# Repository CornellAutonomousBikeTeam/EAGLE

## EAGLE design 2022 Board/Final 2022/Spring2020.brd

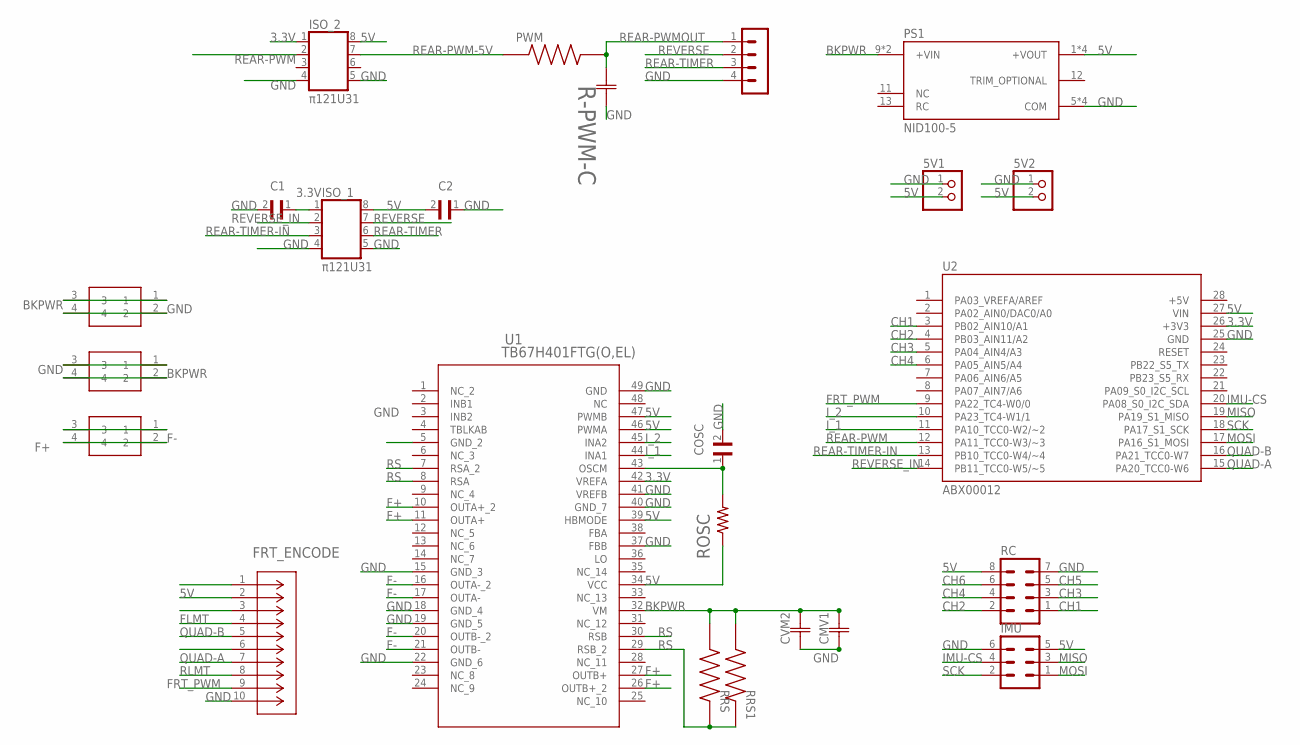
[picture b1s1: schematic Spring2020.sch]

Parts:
5V1, 5V2: PINHD-1X2; 1X02
C1, C2: CL05A105KP5NNNC; CAPC1005X55N
CMV1: UVY1H102MHD; CAP_12.5_X_25_NCH
COSC: GRM022R71A271KA01L; CAPC0402X22N
CVM2: CL05B104KB54PNC; CAP_CL_05_SAM
FRT_ENCODE: 3220-10-0100-00; CONN_3220-10-0100-00_CNC
FRT_MTR: 2060-452_998-404; 2060452998404
IMU: MA03-2
ISO_1, ISO_2: π121U31; SO08
PS1: NID100-5; CONV_NID100-5
PWM: ERJ1GNF6802C; RES_ERJ1GNF6802C
PWR_IN: 2060-452_998-404; 2060452998404
R-PWM-C: CL03A105MQ3CSNC; CAP_CL03_SAM
RC: MA04-2
REAR-MOTOR: MA04-1
REAR_PWR: 2060-452_998-404; 2060452998404
ROSC: R-US_R0402; R0402
RRS, RRS1: RLP73K3AR22FTDF; RESC6331X70N
U1: TB67H401FTG(O,EL); P-VQFN48-0707-0P50-004_TOS
U2: ABX00012; ARDUINO_ABX00012

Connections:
3.3V: C1.1, ISO_1.1, ISO_2.1, U1.42 (VREFA), U2.26 (+3V3)
5V: 5V1.2, 5V2.2, C2.2, FRT_ENCODE.2, IMU.5, ISO_1.8, ISO_2.8, PS1.1 (+VOUT), PS1.2 (+VOUT), PS1.3 (+VOUT), PS1.4 (+VOUT), RC.8, ROSC.1, U1.34 (VCC), U1.39 (HBMODE), U1.46 (PWMA), U1.47 (PWMB), U2.27 (VIN)
+5V: U2.28 (+5V)
BKPWR: CMV1.2, CVM2.2, PS1.9 (+VIN), PS1.10 (+VIN), PWR_IN.1, PWR_IN.3, REAR_PWR.2, REAR_PWR.4, RRS.1, RRS1.1, U1.32 (VM)
CH1: RC.1, U2.3 (PB02_AIN10/A1)
CH2: RC.2, U2.4 (PB03_AIN11/A2)
CH3: RC.3, U2.5 (PA04_AIN4/A3)
CH4: RC.4, U2.6 (PA05_AIN5/A4)
CH5: RC.5
CH6: RC.6
F+: FRT_MTR.2, FRT_MTR.4, U1.10 (OUTA+_2), U1.11 (OUTA+), U1.26 (OUTB+_2), U1.27 (OUTB+)
F-: FRT_MTR.1, FRT_MTR.3, U1.16 (OUTA-_2), U1.17 (OUTA-), U1.20 (OUTB-_2), U1.21 (OUTB-)
FLMT: FRT_ENCODE.4
FRT_PWM: FRT_ENCODE.9, U2.9 (PA22_TC4-W0/0)
GND: 5V1.1, 5V2.1, C1.2, C2.1, CMV1.1, COSC.2, CVM2.1, FRT_ENCODE.10, IMU.6, ISO_1.4, ISO_1.5, ISO_2.4, ISO_2.5, PS1.5 (COM), PS1.6 (COM), PS1.7 (COM), PS1.8 (COM), PWR_IN.2, PWR_IN.4, R-PWM-C.2, RC.7, REAR-MOTOR.4, REAR_PWR.1, REAR_PWR.3, U1.5 (GND_2), U1.15 (GND_3), U1.18 (GND_4), U1.19 (GND_5), U1.22 (GND_6), U1.37 (FBB), U1.40 (GND_7), U1.41 (VREFB), U1.49 (GND), U2.25 (GND)
IMU-CS: IMU.4, U2.20 (PA08_S0_I2C_SDA)
I_1: U1.44 (INA1), U2.11 (PA10_TCC0-W2/~2)
I_2: U1.45 (INA2), U2.10 (PA23_TC4-W1/1)
MISO: IMU.3, U2.19 (PA19_S1_MISO)
MOSI: IMU.1, U2.17 (PA16_S1_MOSI)
OSCM: COSC.1, ROSC.2, U1.43 (OSCM)
QUAD-A: FRT_ENCODE.7, U2.15 (PA20_TCC0-W6)
QUAD-B: FRT_ENCODE.5, U2.16 (PA21_TCC0-W7)
REAR-PWM: ISO_2.2, U2.12 (PA11_TCC0-W3/~3)
REAR-PWM-5V: ISO_2.7, PWM.1
REAR-PWMOUT: PWM.2, R-PWM-C.1, REAR-MOTOR.1
REAR-TIMER: ISO_1.6, REAR-MOTOR.3
REAR-TIMER-IN: ISO_1.3, U2.13 (PB10_TCC0-W4/~4)
REVERSE: ISO_1.7, REAR-MOTOR.2
REVERSE_IN: ISO_1.2, U2.14 (PB11_TCC0-W5/~5)
RLMT: FRT_ENCODE.8
RS: RRS.2, RRS1.2, U1.7 (RSA_2), U1.8 (RSA), U1.29 (RSB_2), U1.30 (RSB)
SCK: IMU.2, U2.18 (PA17_S1_SCK)

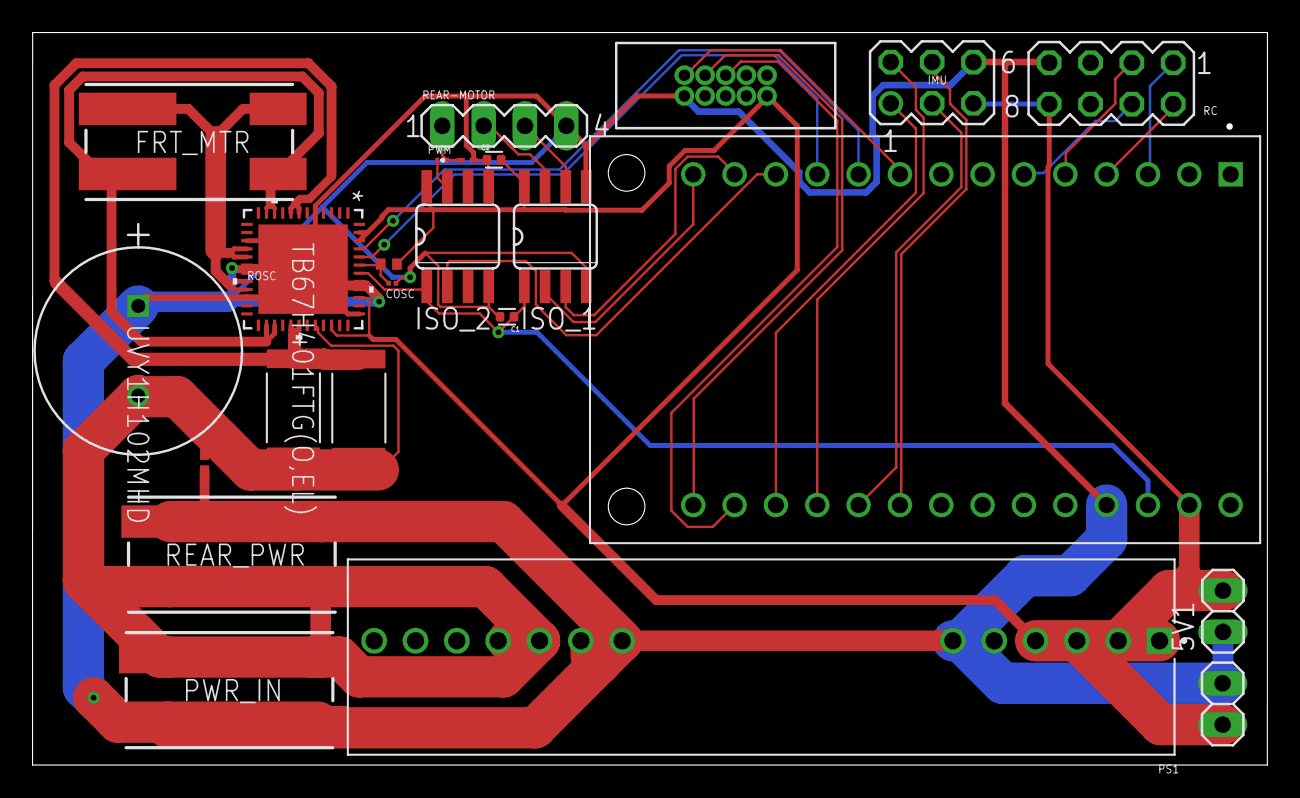
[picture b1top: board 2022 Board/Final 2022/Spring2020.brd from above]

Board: 2 copper layers, 75.9 x 45.0 mm, 24 parts (0 on the bottom side), 28 nets.

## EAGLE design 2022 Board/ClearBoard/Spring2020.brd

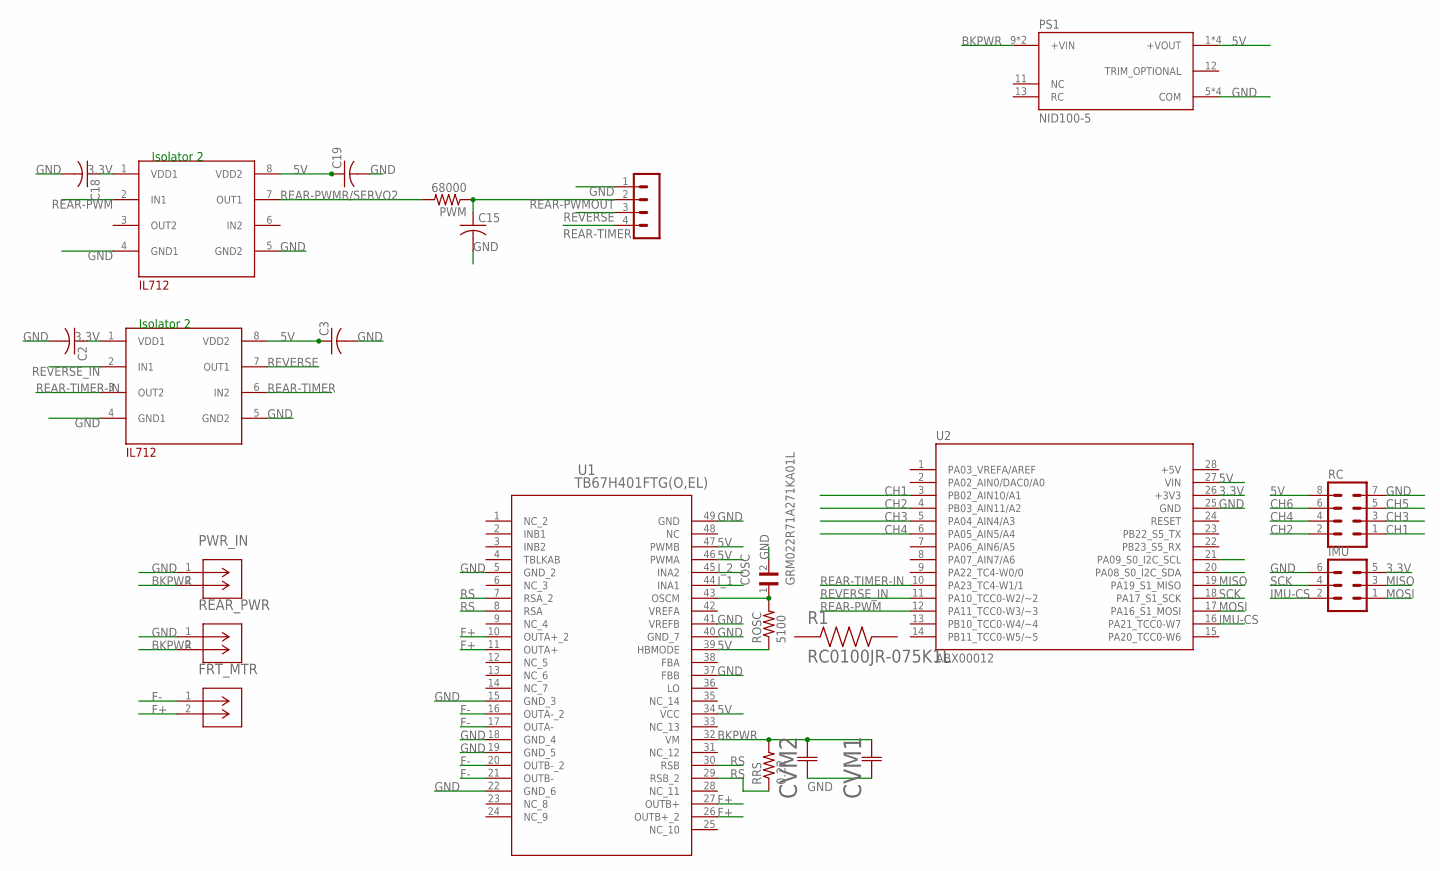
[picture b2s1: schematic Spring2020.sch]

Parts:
C2, C3, C15, C18, C19: C-US025-050X050; C025-050X050
COSC: GRM022R71A271KA01L; CAPC0402X22N
CVM1: 860010674014; CAP_4014_WRE
CVM2: CL05B104KB54PNC; CAP_CL_05_SAM
FRT_MTR: 1792863; CONN_1792863_PXC
IMU: MA03-2
PS1: NID100-5; CONV_NID100-5
PWM: 68000; 0204V
PWR_IN: 1792863; CONN_1792863_PXC
R1: RC0100JR-075K1L; RESC0402X15N
RC: MA04-2
REAR-MOTOR: MA04-1
REAR_PWR: 1792863; CONN_1792863_PXC
ROSC: 5100; 0204V
RRS: 0.22; 0204V
U1: TB67H401FTG(O,EL); P-VQFN48-0707-0P50-004_TOS
U2: ABX00012; ARDUINO_ABX00012
U$2, U$7: IL-712; 8PINSOIC

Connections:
3.3V: C2.1, C18.1, IMU.5, U2.26 (+3V3), U$2.1 (VDD1), U$7.1 (VDD1)
5V: C3.1, C19.1, PS1.1 (+VOUT), PS1.2 (+VOUT), PS1.3 (+VOUT), PS1.4 (+VOUT), RC.8, ROSC.1, U1.34 (VCC), U1.39 (HBMODE), U1.46 (PWMA), U1.47 (PWMB), U2.27 (VIN), U$2.8 (VDD2), U$7.8 (VDD2)
+5V: U2.28 (+5V)
BKPWR: CVM1.2, CVM2.2, PS1.9 (+VIN), PS1.10 (+VIN), PWR_IN.2, REAR_PWR.2, RRS.2, U1.32 (VM)
CH1: RC.1, U2.3 (PB02_AIN10/A1)
CH2: RC.2, U2.4 (PB03_AIN11/A2)
CH3: RC.3, U2.5 (PA04_AIN4/A3)
CH4: RC.4, U2.6 (PA05_AIN5/A4)
CH5: RC.5
CH6: RC.6
F+: FRT_MTR.2, U1.10 (OUTA+_2), U1.11 (OUTA+), U1.26 (OUTB+_2), U1.27 (OUTB+)
F-: FRT_MTR.1, U1.16 (OUTA-_2), U1.17 (OUTA-), U1.20 (OUTB-_2), U1.21 (OUTB-)
GND: C2.2, C3.2, C15.2, C18.2, C19.2, COSC.2, CVM1.1, CVM2.1, IMU.6, PS1.5 (COM), PS1.6 (COM), PS1.7 (COM), PS1.8 (COM), PWR_IN.1, RC.7, REAR-MOTOR.1, REAR_PWR.1, U1.5 (GND_2), U1.15 (GND_3), U1.18 (GND_4), U1.19 (GND_5), U1.22 (GND_6), U1.37 (FBB), U1.40 (GND_7), U1.41 (VREFB), U1.49 (GND), U2.25 (GND), U$2.4 (GND1), U$2.5 (GND2), U$7.4 (GND1), U$7.5 (GND2)
IMU-CS: IMU.2, U2.16 (PA21_TCC0-W7)
I_1: U1.44 (INA1)
I_2: U1.45 (INA2)
MISO: IMU.3, U2.19 (PA19_S1_MISO)
MOSI: IMU.1, U2.17 (PA16_S1_MOSI)
unnamed: COSC.1, ROSC.2, U1.43 (OSCM)
REAR-PWM: U2.12 (PA11_TCC0-W3/~3), U$7.2 (IN1)
REAR-PWMOUT: C15.1, PWM.1, REAR-MOTOR.2
REAR-PWMR/SERVO2: PWM.2, U$7.7 (OUT1)
REAR-TIMER: REAR-MOTOR.4, U$2.6 (IN2)
REAR-TIMER-IN: U2.10 (PA23_TC4-W1/1), U$2.3 (OUT2)
REVERSE: REAR-MOTOR.3, U$2.7 (OUT1)
REVERSE_IN: U2.11 (PA10_TCC0-W2/~2), U$2.2 (IN1)
RS: RRS.1, U1.7 (RSA_2), U1.8 (RSA), U1.29 (RSB_2), U1.30 (RSB)
SCK: IMU.4, U2.18 (PA17_S1_SCK)
VREFA: U1.42 (VREFA)

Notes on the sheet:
Isolator 2

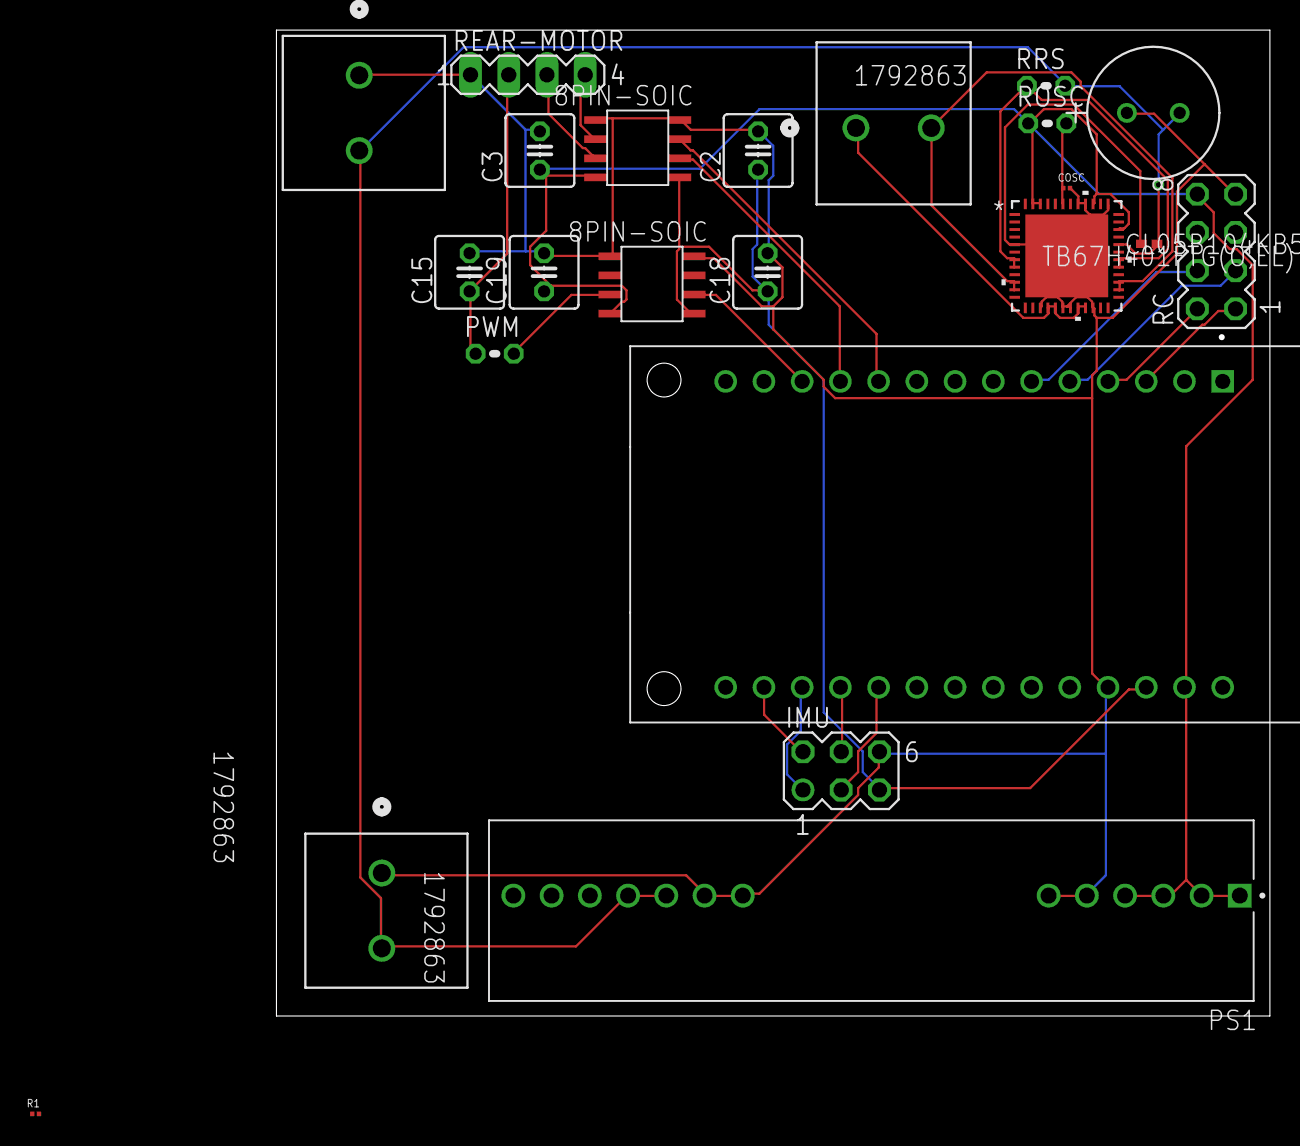
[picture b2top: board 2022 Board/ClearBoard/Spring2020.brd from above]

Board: 2 copper layers, 66.0 x 65.5 mm, 23 parts (0 on the bottom side), 23 nets.

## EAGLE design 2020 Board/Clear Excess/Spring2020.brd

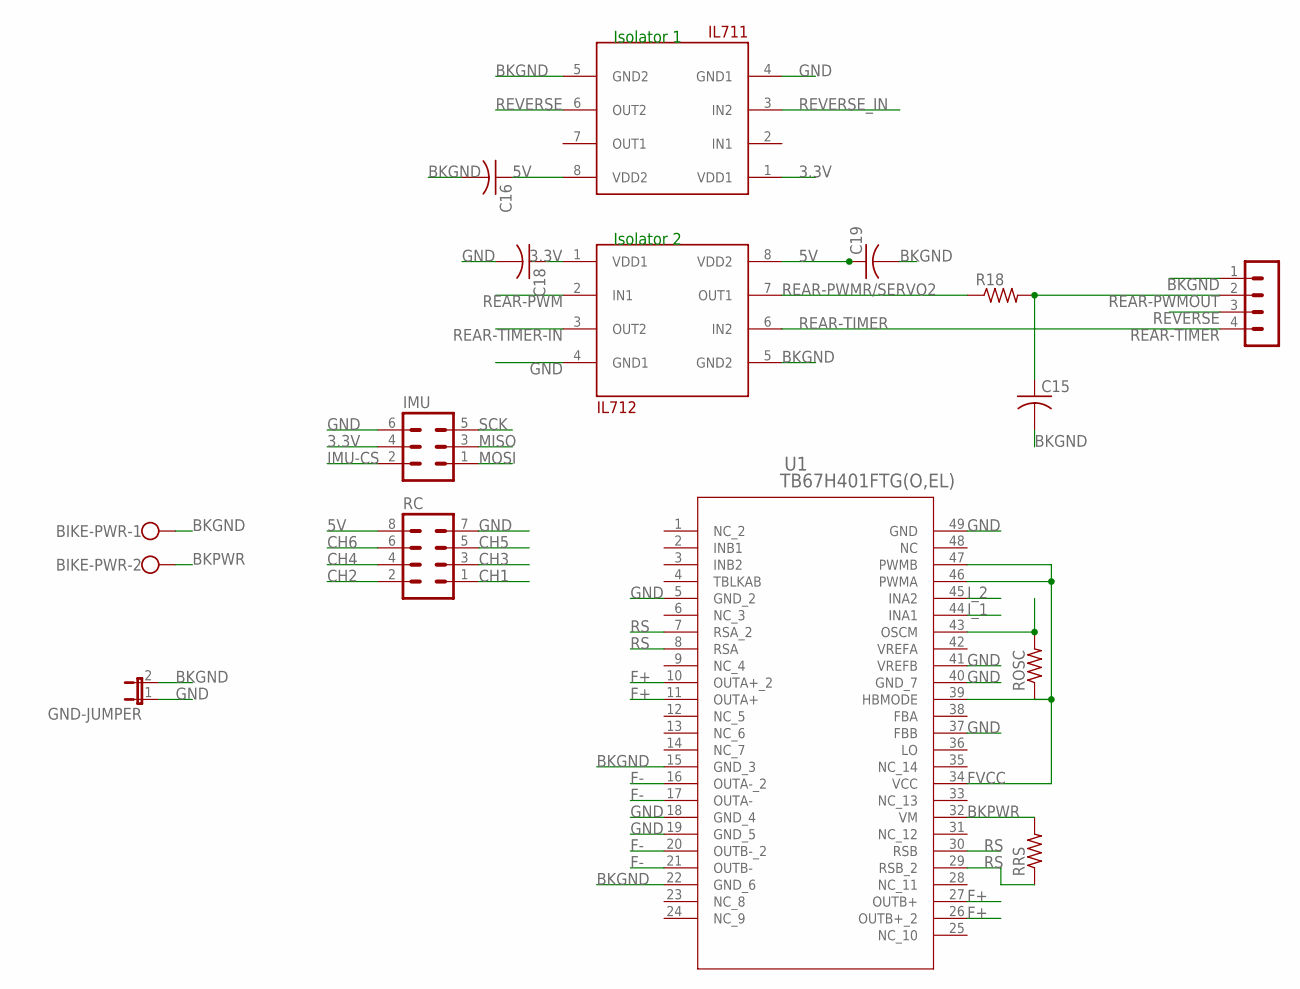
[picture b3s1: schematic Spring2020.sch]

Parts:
BIKE-PWR: W237-102
C15, C16, C18, C19: C-US025-050X050; C025-050X050
GND-JUMPER: JP1E; JP1
IMU: MA03-2
R18: R-US_0414/15; 0414/15
RC: MA04-2
REAR-MOTOR: MA04-1
ROSC: R-US_0309/10; 0309/10
RRS: R-US_0309/10; 0309/10
U1: TB67H401FTG(O,EL); P-VQFN48-0707-0P50-004_TOS
U$2: IL-711; 8PINSOIC
U$7: IL-712; 8PINSOIC

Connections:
3.3V: C18.1, IMU.4, U$2.1 (VDD1), U$7.1 (VDD1)
5V: C16.1, C19.1, RC.8, U$2.8 (VDD2), U$7.8 (VDD2)
BKGND: BIKE-PWR.1, C15.2, C16.2, C19.2, GND-JUMPER.2, REAR-MOTOR.1, U1.15 (GND_3), U1.22 (GND_6), U$2.5 (GND2), U$7.5 (GND2)
BKPWR: BIKE-PWR.2, RRS.2, U1.32 (VM)
CH1: RC.1
CH2: RC.2
CH3: RC.3
CH4: RC.4
CH5: RC.5
CH6: RC.6
F+: U1.10 (OUTA+_2), U1.11 (OUTA+), U1.26 (OUTB+_2), U1.27 (OUTB+)
F-: U1.16 (OUTA-_2), U1.17 (OUTA-), U1.20 (OUTB-_2), U1.21 (OUTB-)
FVCC: ROSC.1, U1.34 (VCC), U1.39 (HBMODE), U1.46 (PWMA), U1.47 (PWMB)
GND: C18.2, GND-JUMPER.1, IMU.6, RC.7, U1.5 (GND_2), U1.18 (GND_4), U1.19 (GND_5), U1.37 (FBB), U1.40 (GND_7), U1.41 (VREFB), U1.49 (GND), U$2.4 (GND1), U$7.4 (GND1)
IMU-CS: IMU.2
I_1: U1.44 (INA1)
I_2: U1.45 (INA2)
MISO: IMU.3
MOSI: IMU.1
unnamed: ROSC.2, U1.43 (OSCM)
REAR-PWM: U$7.2 (IN1)
REAR-PWMOUT: C15.1, R18.2, REAR-MOTOR.2
REAR-PWMR/SERVO2: R18.1, U$7.7 (OUT1)
REAR-TIMER: REAR-MOTOR.4, U$7.6 (IN2)
REAR-TIMER-IN: U$7.3 (OUT2)
REVERSE: REAR-MOTOR.3, U$2.6 (OUT2)
REVERSE_IN: U$2.3 (IN2)
RS: RRS.1, U1.7 (RSA_2), U1.8 (RSA), U1.29 (RSB_2), U1.30 (RSB)
SCK: IMU.5
VREFA: U1.42 (VREFA)

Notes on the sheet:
Isolator 1
Isolator 2

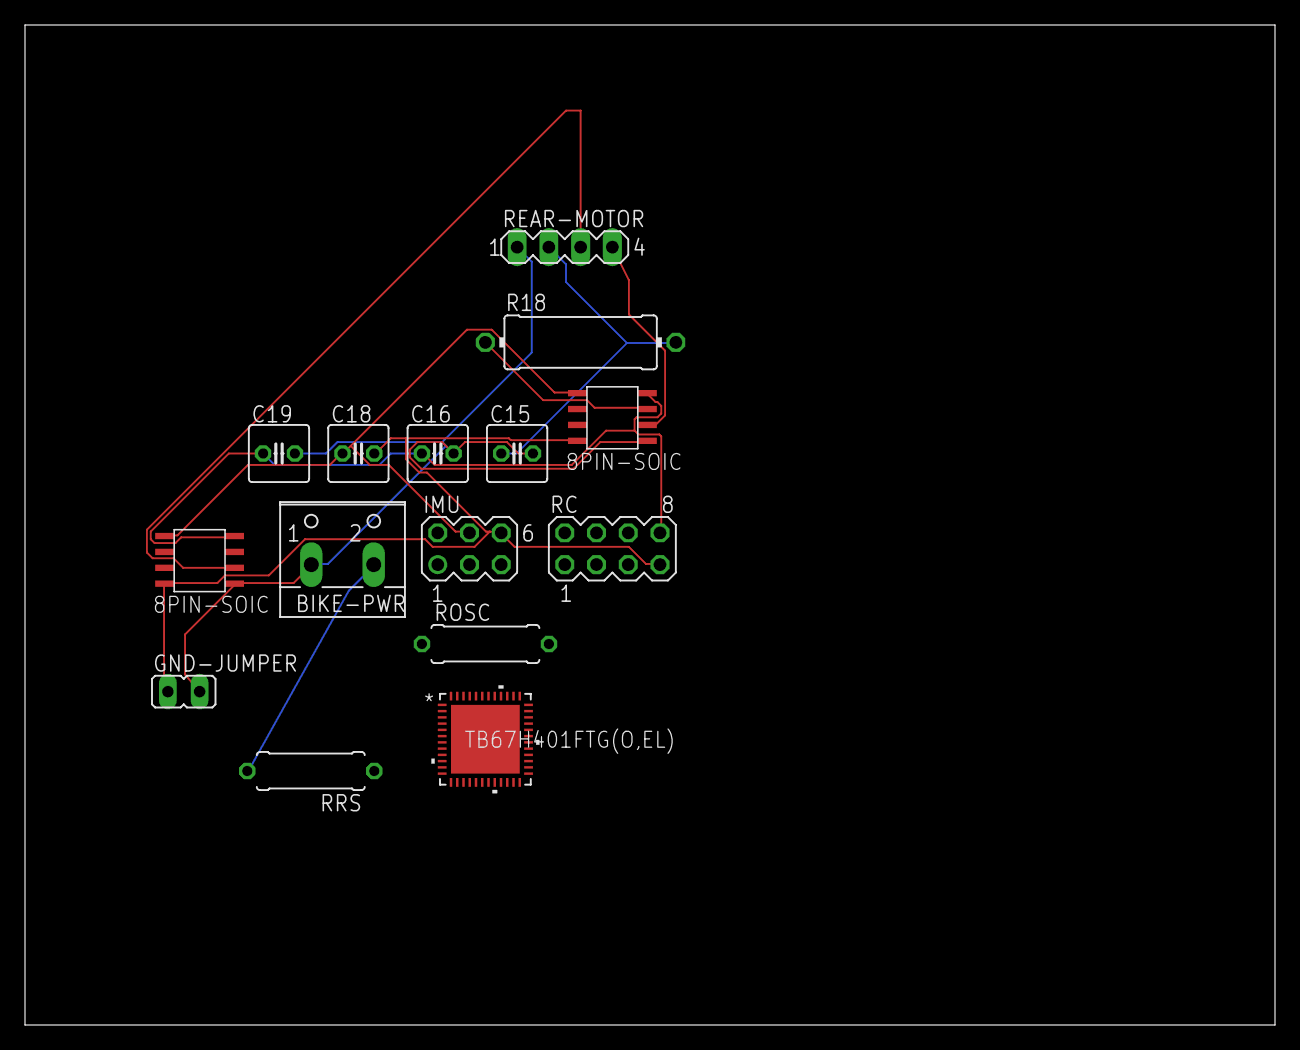
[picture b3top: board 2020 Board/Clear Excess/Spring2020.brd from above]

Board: 2 copper layers, 100.0 x 80.0 mm, 15 parts (0 on the bottom side), 14 nets.

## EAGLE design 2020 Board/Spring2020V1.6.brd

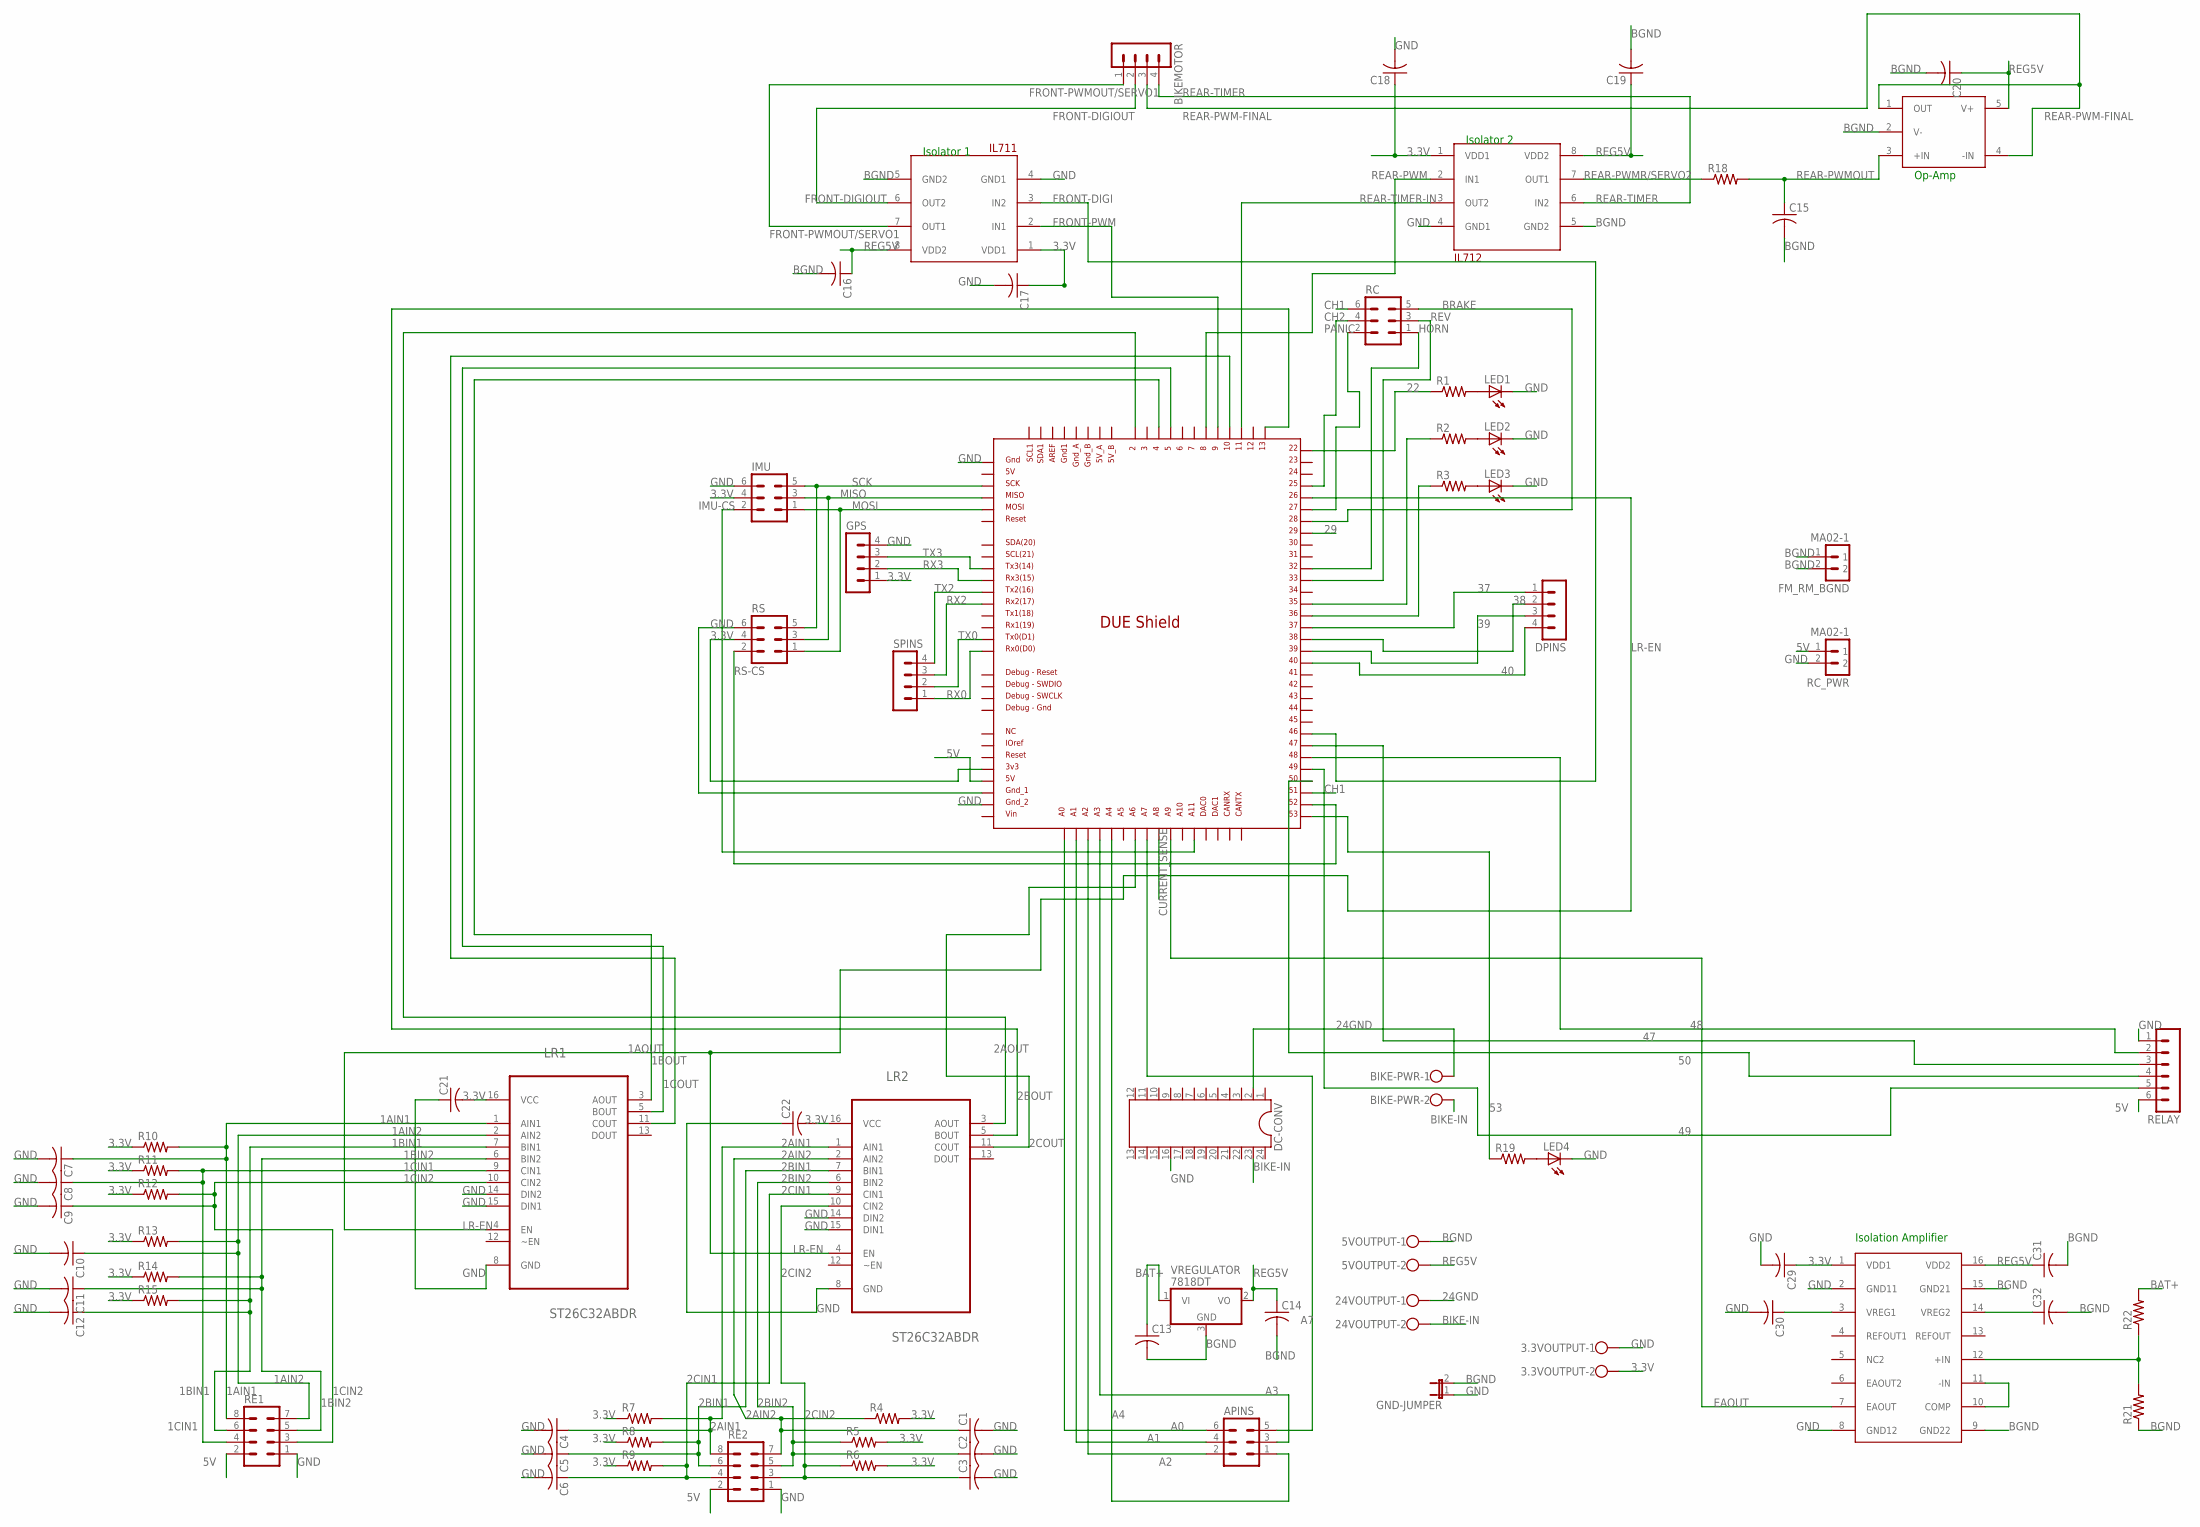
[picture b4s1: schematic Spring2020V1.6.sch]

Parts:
3.3VOUTPUT, 5VOUTPUT, 24VOUTPUT: W237-102
APINS: MA03-2
BIKE-PWR: W237-102
BIKEMOTOR: MA04-1
C1, C2, C3, C4, C5, C6, C7, C8, C9, C10, C11, C12: C-US025-025X050; C025-025X050
C13, C14, C15, C16, C17, C18, C19, C20, C21, C22, C29, C30, C31, C32: C-US025-050X050; C025-050X050
DC-CONV: CU.INC---VAWQ6-Q48-S12H-6; DIL24-6
DPINS: MA04-1
FM_RM_BGND: MA02-1
GND-JUMPER: JP1E; JP1
GPS: MA04-1
IMU: MA03-2
LED1, LED2, LED3, LED4: LED5MM
LR1, LR2: ST26C32ABDR; SOIC127P600X175-16N
OP-AMP: OPAMP; SOT95P280X145-5N
R1, R2, R3, R19: R-US_0309/10; 0309/10
R4, R5, R6, R7, R8, R9, R10, R11, R12, R13, R14, R15: R-US_0613/15; P0613/15
R18, R21, R22: R-US_0414/15; 0414/15
RC: MA03-2
RC_PWR: MA02-1
RE1, RE2: MA04-2
RELAY: MA06-1
RS: MA03-2
SPINS: MA04-1
U$1: DUE(NORMAL)
U$2: IL-711; 8PINSOIC
U$5: ISOLATED_ERROR_AMP_ADUM3190; QSOP16
U$7: IL-712; 8PINSOIC
VREGULATOR: 7818DT; TO252

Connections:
1AIN1: C7.1, LR1.1 (AIN1), R10.2, RE1.8
1AIN2: C10.1, LR1.2 (AIN2), R13.2, RE1.7
1AOUT: LR1.3 (AOUT), U$1.4
1BIN1: C12.1, LR1.7 (BIN1), R15.2, RE1.6
1BIN2: C11.1, LR1.6 (BIN2), R14.2, RE1.5
1BOUT: LR1.5 (BOUT), U$1.5
1CIN1: C8.1, LR1.9 (CIN1), R11.2, RE1.4
1CIN2: C9.1, LR1.10 (CIN2), R12.2, RE1.3
1COUT: LR1.11 (COUT), U$1.10
2AIN1: C4.1, LR2.1 (AIN1), R7.2, RE2.8
2AIN2: C1.1, LR2.2 (AIN2), R4.1, RE2.7
2AOUT: LR2.3 (AOUT), U$1.2
2BIN1: C5.1, LR2.7 (BIN1), R8.2, RE2.6
2BIN2: C2.1, LR2.6 (BIN2), R5.1, RE2.5
2BOUT: LR2.5 (BOUT), U$1.13
2CIN1: C6.1, LR2.9 (CIN1), R9.2, RE2.4
2CIN2: C3.1, LR2.10 (CIN2), R6.1, RE2.3
2COUT: LR2.11 (COUT), U$1.A6
3.3V: 3.3VOUTPUT.2, C17.1, C18.1, C21.2, C22.2, C29.1, GPS.1, IMU.4, LR1.16 (VCC), LR2.16 (VCC), R4.2, R5.2, R6.2, R7.1, R8.1, R9.1, R10.1, R11.1, R12.1, R13.1, R14.1, R15.1, RS.4, U$1.3V3, U$2.1 (VDD1), U$5.1 (VDD1), U$7.1 (VDD1)
5V: RC_PWR.1, RE1.2, RE2.2, RELAY.6, U$1.5V
22: R1.1, U$1.22
24GND: 24VOUTPUT.1, BIKE-PWR.1, DC-CONV.2
29: U$1.29
35: R2.1, U$1.35
36: R3.1, U$1.36
37: DPINS.1, U$1.37
38: DPINS.2, U$1.38
39: DPINS.3, U$1.39
40: DPINS.4, U$1.40
47: RELAY.3, U$1.47
48: RELAY.2, U$1.48
49: RELAY.5, U$1.49
50: RELAY.4, U$1.50
53: R19.1, U$1.53
A0: APINS.6, U$1.A0
A1: APINS.4, U$1.A1
A2: APINS.2, U$1.A2
A3: APINS.3, U$1.A3
A4: APINS.1, U$1.A4
A7: APINS.5, U$1.A7
BAT+: C13.1, R22.2, VREGULATOR.1 (VI)
BGND: 5VOUTPUT.1, C13.2, C14.2, C15.2, C16.2, C19.2, C20.2, C31.2, C32.2, FM_RM_BGND.1, FM_RM_BGND.2, GND-JUMPER.2, OP-AMP.2 (V-), R21.1, U$2.5 (GND2), U$5.9 (GND22), U$5.15 (GND21), U$7.5 (GND2), VREGULATOR.3 (GND)
BIKE-IN: 24VOUTPUT.2, BIKE-PWR.2, DC-CONV.23
BRAKE: RC.5, U$1.28
CH1: RC.6, U$1.51
CH2: RC.4, U$1.25
CURRENT_SENSE: U$1.A8
EAOUT: U$1.A9, U$5.7 (EAOUT)
FRONT-DIGI: U$1.46, U$2.3 (IN2)
FRONT-DIGIOUT: BIKEMOTOR.2, U$2.6 (OUT2)
FRONT-PWM: U$1.9, U$2.2 (IN1)
FRONT-PWMOUT/SERVO1: BIKEMOTOR.1, U$2.7 (OUT1)
GND: 3.3VOUTPUT.1, C1.2, C2.2, C3.2, C4.2, C5.2, C6.2, C7.2, C8.2, C9.2, C10.2, C11.2, C12.2, C17.2, C18.2, C21.1, C22.1, C29.2, C30.2, DC-CONV.16, GND-JUMPER.1, GPS.4, IMU.6, LED1.K (C), LED2.K (C), LED3.K (C), LED4.K (C), LR1.8 (GND), LR1.14 (DIN2), LR1.15 (DIN1), LR2.8 (GND), LR2.14 (DIN2), LR2.15 (DIN1), RC_PWR.2, RE1.1, RE2.1, RELAY.1, RS.6, U$1.5V_ICSP, U$1.GND_1, U$1.GND_2, U$2.4 (GND1), U$5.2 (GND11), U$5.8 (GND12), U$7.4 (GND1)
HORN: RC.1, U$1.32
IMU-CS: IMU.2, U$1.A11
LR-EN: LR1.4 (EN), LR2.4 (EN), U$1.26
MISO: IMU.3, RS.3, U$1.MISO_ICSP
MOSI: IMU.1, RS.1, U$1.MOSI_ICSP
unnamed: LED1.A, R1.2
unnamed: LED2.A, R2.2
unnamed: LED3.A, R3.2
unnamed: LED4.A, R19.2
unnamed: C32.1, U$5.14 (VREG2)
unnamed: U$5.10 (COMP), U$5.11 (-IN)
unnamed: R21.2, R22.1, U$5.12 (+IN)
unnamed: C30.1, U$5.3 (VREG1)
PANIC: RC.2, U$1.27
REAR-PWM: U$1.8, U$7.2 (IN1)
REAR-PWM-FINAL: BIKEMOTOR.3, OP-AMP.1 (OUT), OP-AMP.4 (-IN)
REAR-PWMOUT: C15.1, OP-AMP.3 (+IN), R18.2
REAR-PWMR/SERVO2: R18.1, U$7.7 (OUT1)
REAR-TIMER: BIKEMOTOR.4, U$7.6 (IN2)
REAR-TIMER-IN: U$1.11, U$7.3 (OUT2)
REG5V: 5VOUTPUT.2, C14.1, C16.1, C19.1, C20.1, C31.1, OP-AMP.5 (V+), U$2.8 (VDD2), U$5.16 (VDD2), U$7.8 (VDD2), VREGULATOR.2 (VO)
REV: RC.3, U$1.33
RS-CS: RS.2, U$1.52
RX0: SPINS.1, U$1.RX0
RX2: SPINS.3, U$1.RX2
RX3: GPS.2, U$1.RX3
SCK: IMU.5, RS.5, U$1.SCK_ICSP
TX0: SPINS.2, U$1.TX0
TX2: SPINS.4, U$1.TX2
TX3: GPS.3, U$1.TX3

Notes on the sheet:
Op-Amp
Isolator 1
Isolator 2
Isolation Amplifier

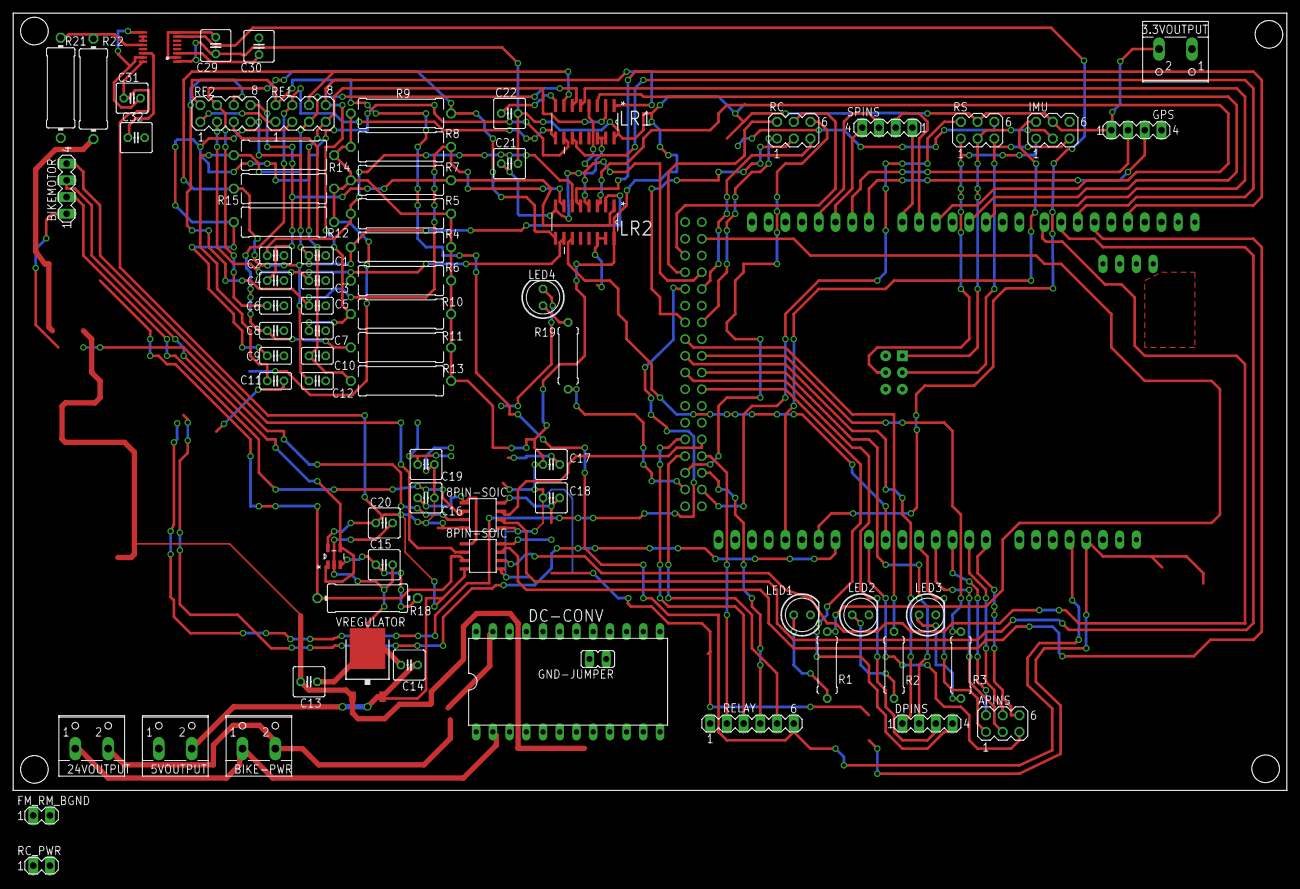
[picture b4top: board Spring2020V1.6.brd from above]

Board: 2 copper layers, 193.5 x 118.1 mm, 76 parts (1 on the bottom side), 81 nets.

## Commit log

2020-04-25 Removed WD PINS and WATCHDOG
    Removed the WD PINS and connected Op-Amp from the PCB.
2020-04-25 Remove H-Bridges, Sail Power, and Sail Motor
    Important to note: couldnt use toprouter and had to use a different route
2020-04-26 Banned POT and removed LED 5
    Removed the POT (potentiometer) pin-out ports, LED 5, and assosciated wiring from the PCB.
2020-05-03 Remove the VIN and PWR Jumper
2020-05-03 Modified SERVO1/SERVO2 and added RC_PWR
2020-10-19 Add files via upload
    Modified configuration of components in .brd file and update routes.
2022-03-14 Some Export Testing
2022-03-22 Reorganized Files
2022-03-22 DC DC Updated
    DC/DC updated
2022-03-27 Started cutting down old board
2022-03-29 Started building up new board & cleanup
2022-03-29 Some more cleanup
2022-04-11 Final Cleaning of Bike
2022-04-17 MCR
    Added the front motor controller, once clarification comes in on the isolator, can deal with the isolator connection as well
2022-04-18 Added front motor
2022-04-18 Added routing
2022-04-25 Lots of stuff
2022-05-01 Fixed a bunch of stuff
    Routed most of the board
2022-05-02 Almost done with place and route
2022-05-03 Finished front motor attachments
    Also positioned things in board
2022-05-07 Almost completely working board
2022-05-13 Just a few random edits
2022-09-20 DONE!
2022-10-16 Almost done
2022-11-08 Changed IMU voltage

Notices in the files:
parts and their libraries:
COPYRIGHT: Copyright (C) 2022 Ultra Librarian. All rights reserved.
